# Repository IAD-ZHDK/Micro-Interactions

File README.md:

# Micro-Interactions
An LED playball for learning basic soldering
First used for a workshop at the ZHdK Open Day in 2014

All pins need to be cut flush with the PCB, to avoid contacting the battery on the back side of the PCB!

The plastic balls are 35mm diameter "chewing gum Machine" capsules, available from this distributer
https://sonesta-automaten.de/

# Schematic 

# Origial Poster image

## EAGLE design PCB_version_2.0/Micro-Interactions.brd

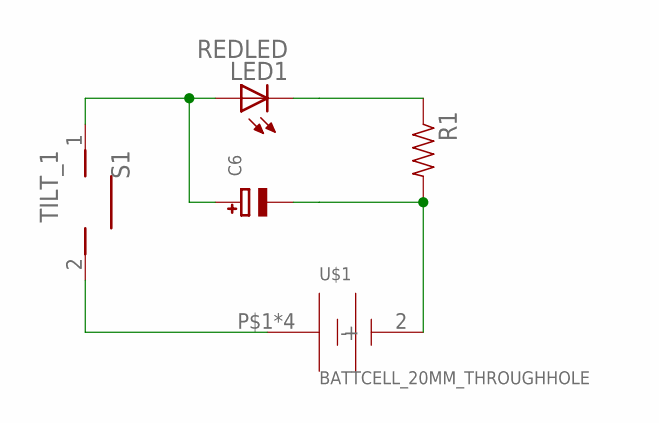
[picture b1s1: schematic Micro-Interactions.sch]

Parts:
C6: CAP_ELECTROLYTICPTH_3.5MMGRID_8MMDIA; CELEC_3.5MM_8MM
LED1: REDLED; LED5MM
R1: RESISTORAXIAL-0.3; AXIAL-0.3
S1: TILT_1; DS-01
U$1: BATTCELL_20MM_THROUGHHOLE; BATTCON_20MM_4LEGS

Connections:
unnamed: C6.+, LED1.A, S1.1
unnamed: LED1.K (C), R1.P$1 (1)
unnamed: S1.2, U$1.P$1 (+), U$1.P$2 (+), U$1.P$3 (+), U$1.P$4 (+)
unnamed: C6.-, R1.P$2 (2), U$1.2 (-)

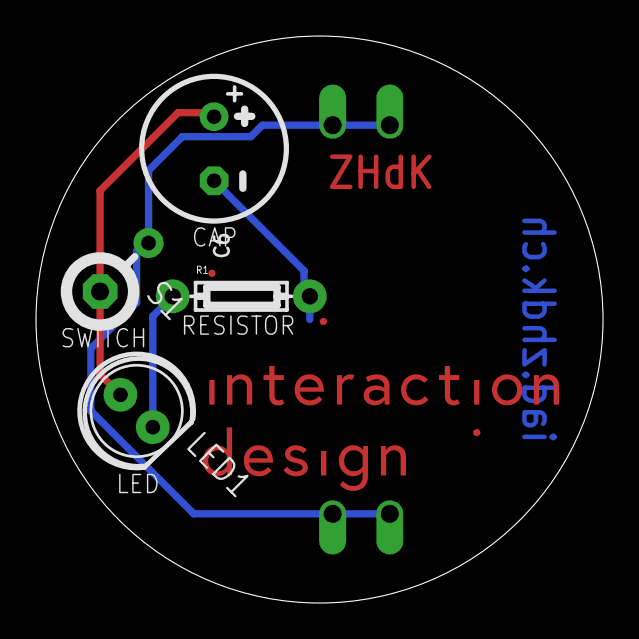
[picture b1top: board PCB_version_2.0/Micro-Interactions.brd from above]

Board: 2 copper layers, 31.5 x 31.5 mm, 6 parts (1 on the bottom side), 4 nets.

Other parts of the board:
U$2: IADLOGO_20MM

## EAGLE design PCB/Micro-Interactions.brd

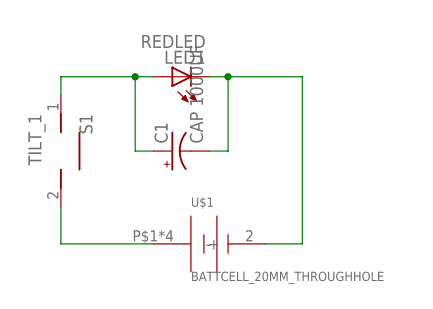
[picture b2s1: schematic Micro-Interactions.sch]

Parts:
C1: CAP 1000UF; CPOL-RADIAL-1000UF-25V
LED1: REDLED; LED5MM
S1: TILT_1; DS-01
U$1: BATTCELL_20MM_THROUGHHOLE; BATTCON_20MM_4LEGS

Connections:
unnamed: C1.1 (+), LED1.A, S1.1
unnamed: C1.2 (-), LED1.K (C), U$1.2 (-)
unnamed: S1.2, U$1.P$1 (+), U$1.P$2 (+), U$1.P$3 (+), U$1.P$4 (+)

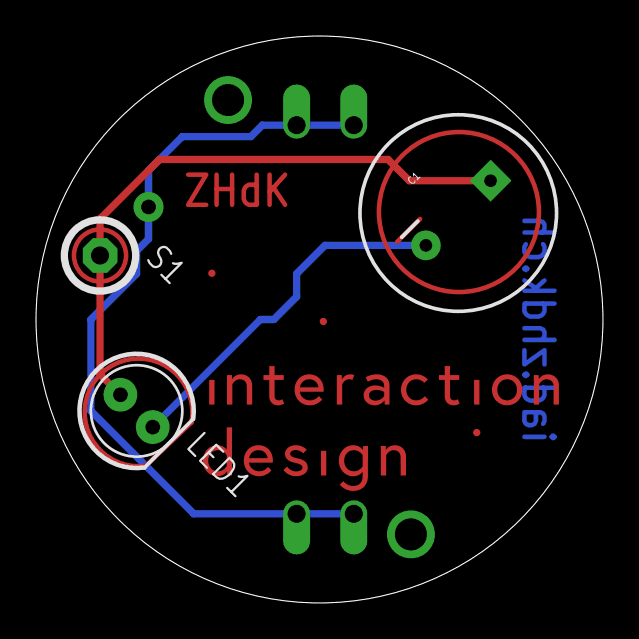
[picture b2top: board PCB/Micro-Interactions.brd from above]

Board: 2 copper layers, 31.5 x 31.5 mm, 5 parts (1 on the bottom side), 3 nets.

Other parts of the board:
U$2: IADLOGO_20MM

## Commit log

2018-02-28 Moved folder
2018-02-28 Graphic Material added
2018-03-05 Removed QR code and added web link to rear side
2019-09-18 image added
2022-10-11 update documentation
2022-10-11 fix image link
2022-10-11 fix schematic imaghe

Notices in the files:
parts and their libraries:
SparkFun-LED: Licensing: CC v3.0 Share-Alike You are welcome to use this library for commercial purposes.
UG_2832HSWEG02: This work is placed in the public domain, and may be freely used for commercial and non-commercial work with the following conditions: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
